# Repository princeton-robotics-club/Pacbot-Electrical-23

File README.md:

View this project on [CADLAB.io](https://cadlab.io/project/26145). 

# Pacbot-Electrical-22-23

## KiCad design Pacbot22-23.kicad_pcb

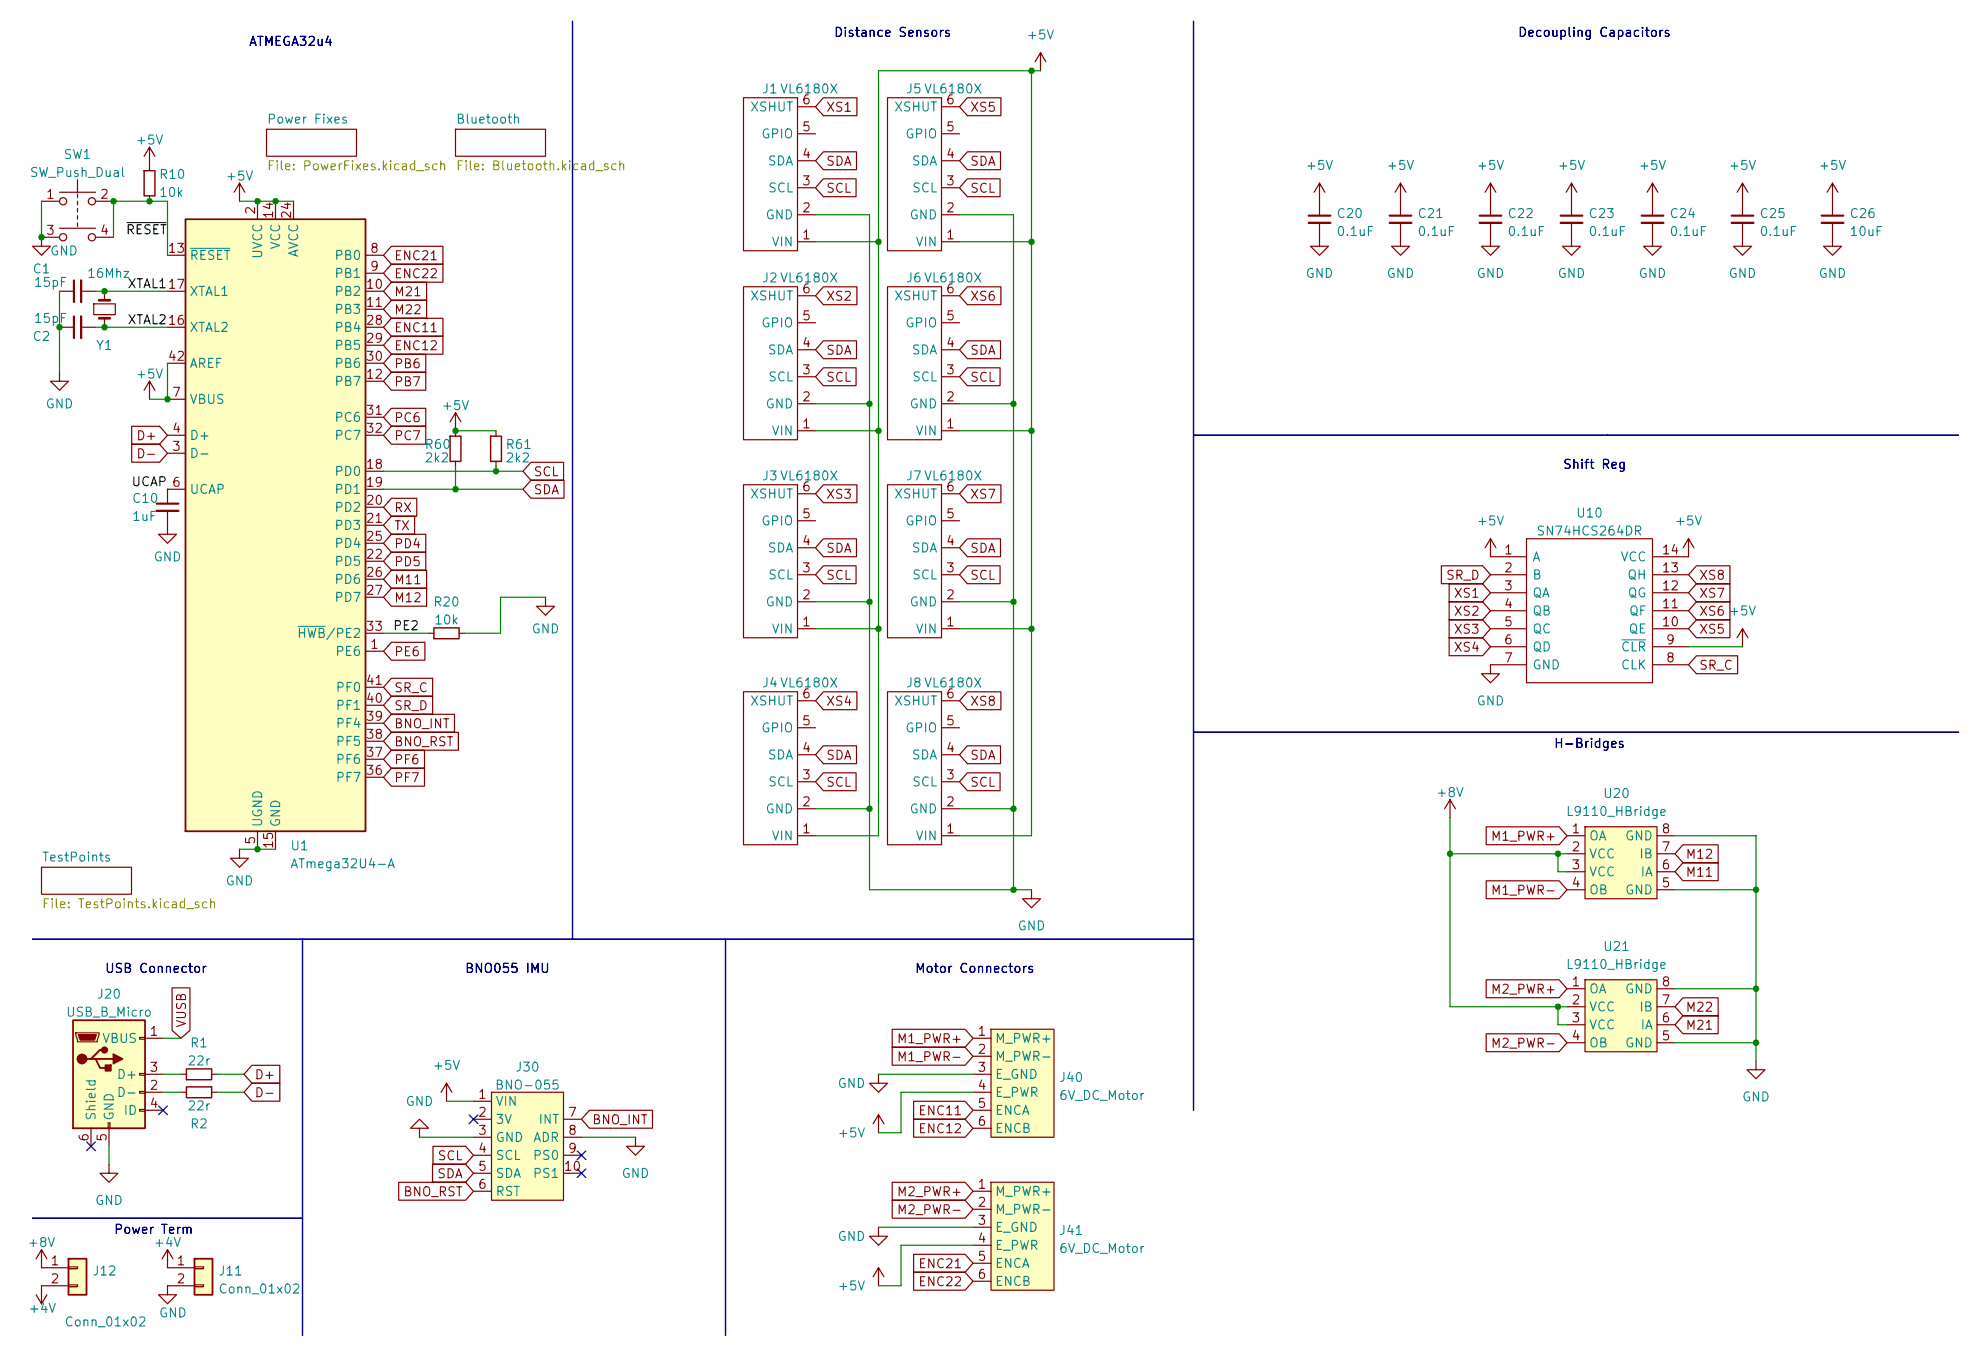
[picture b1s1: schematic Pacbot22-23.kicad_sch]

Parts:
C1, C2: 15pF; C_0805_2012Metric
C10: 1uF; C_0805_2012Metric
C20, C21, C22, C23, C24, C25: 0.1uF; C_0805_2012Metric
C26: 10uF; C_0805_2012Metric
J1, J2, J3, J4, J5, J6, J7, J8: VL6180X
J11, J12: Conn_01x02; POWER_TERM
J20: USB_B_Micro; USB_Micro-B_GCT_USB3076-30-A
J30: BNO-055; BNO055
J40, J41: 6V_DC_Motor
R1, R2: 22r; R_0805_2012Metric
R10, R20: 10k; R_0805_2012Metric
R60, R61: 2k2; R_0805_2012Metric
SW1: SW_Push_Dual; TL3305AF260QG
U1: ATmega32U4-A; TQFP-44_10x10mm_P0.8mm
U10: SN74HCS264DR; SOIC127P600X175-14N; Mouser Part Number 595-SN74HCS264DR
U20, U21: L9110_HBridge; Adafruit_L9110_HBridge
Y1: 16Mhz; Crystal_SMD_5032-2Pin_5.0x3.2mm_HandSoldering

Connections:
+4V: J11.1, J12.2
+5V: C20.1, C21.1, C22.1, C23.1, C24.1, C25.1, C26.1, J1.1 (VIN), J2.1 (VIN), J3.1 (VIN), J4.1 (VIN), J5.1 (VIN), J6.1 (VIN), J7.1 (VIN), J8.1 (VIN), J30.1 (VIN), J40.4 (E_PWR), J41.4 (E_PWR), R10.1, R60.1, R61.1, U1.2 (UVCC), U1.7 (VBUS), U1.14 (VCC), U1.24 (AVCC), U1.34 (VCC), U1.42 (AREF), U1.44 (AVCC), U10.1 (A), U10.9 (~CLR), U10.14 (VCC); also elsewhere on the board
+8V: J12.1, U20.2 (VCC), U20.3 (VCC), U21.2 (VCC), U21.3 (VCC); also elsewhere on the board
/PE2: R20.1, U1.33 (~HWB/PE2)
/UCAP: C10.1, U1.6 (UCAP)
/XTAL1: C1.2, U1.17 (XTAL1), Y1.1
/XTAL2: C2.2, U1.16 (XTAL2), Y1.2
/~RESET: R10.2, SW1.2, SW1.4, U1.13 (~RESET)
BNO_INT: J30.7 (INT), U1.39 (PF4); also elsewhere on the board
BNO_RST: J30.6 (RST), U1.38 (PF5); also elsewhere on the board
D+: R1.2, U1.4 (D+); also elsewhere on the board
D-: R2.1, U1.3 (D-); also elsewhere on the board
ENC11: J40.5 (ENCA), U1.28 (PB4); also elsewhere on the board
ENC12: J40.6 (ENCB), U1.29 (PB5); also elsewhere on the board
ENC21: J41.5 (ENCA), U1.8 (PB0); also elsewhere on the board
ENC22: J41.6 (ENCB), U1.9 (PB1); also elsewhere on the board
GND: C1.1, C2.1, C10.2, C20.2, C21.2, C22.2, C23.2, C24.2, C25.2, C26.2, J1.2 (GND), J2.2 (GND), J3.2 (GND), J4.2 (GND), J5.2 (GND), J6.2 (GND), J7.2 (GND), J8.2 (GND), J11.2, J20.5 (GND), J30.3 (GND), J30.8 (ADR), J40.3 (E_GND), J41.3 (E_GND), R20.2, SW1.1, SW1.3, U1.5 (UGND), U1.15 (GND), U1.23 (GND), U1.35 (GND), U1.43 (GND), U10.7 (GND), U20.5 (GND), U20.8 (GND), U21.5 (GND), U21.8 (GND); also elsewhere on the board
M1_PWR+: J40.1 (M_PWR+), U20.1 (OA)
M1_PWR-: J40.2 (M_PWR-), U20.4 (OB)
M2_PWR+: J41.1 (M_PWR+), U21.1 (OA)
M2_PWR-: J41.2 (M_PWR-), U21.4 (OB)
M11: U1.26 (PD6), U20.6 (IA); also elsewhere on the board
M12: U1.27 (PD7), U20.7 (IB); also elsewhere on the board
M21: U1.10 (PB2), U21.6 (IA); also elsewhere on the board
M22: U1.11 (PB3), U21.7 (IB); also elsewhere on the board
unnamed: J20.2 (D-), R2.2
unnamed: J20.3 (D+), R1.1
PB6: U1.30 (PB6); also elsewhere on the board
PB7: U1.12 (PB7); also elsewhere on the board
PC6: U1.31 (PC6); also elsewhere on the board
PC7: U1.32 (PC7); also elsewhere on the board
PD4: U1.25 (PD4); also elsewhere on the board
PD5: U1.22 (PD5); also elsewhere on the board
PE6: U1.1 (PE6); also elsewhere on the board
PF6: U1.37 (PF6); also elsewhere on the board
PF7: U1.36 (PF7); also elsewhere on the board
RX: U1.20 (PD2); also elsewhere on the board
SCL: J1.3 (SCL), J2.3 (SCL), J3.3 (SCL), J4.3 (SCL), J5.3 (SCL), J6.3 (SCL), J7.3 (SCL), J8.3 (SCL), J30.4 (SCL), R61.2, U1.18 (PD0); also elsewhere on the board
SDA: J1.4 (SDA), J2.4 (SDA), J3.4 (SDA), J4.4 (SDA), J5.4 (SDA), J6.4 (SDA), J7.4 (SDA), J8.4 (SDA), J30.5 (SDA), R60.2, U1.19 (PD1); also elsewhere on the board
SR_C: U1.41 (PF0), U10.8 (CLK); also elsewhere on the board
SR_D: U1.40 (PF1), U10.2 (B); also elsewhere on the board
TX: U1.21 (PD3); also elsewhere on the board
VUSB: J20.1 (VBUS); also elsewhere on the board
XS1: J1.6 (XSHUT), U10.3 (QA)
XS2: J2.6 (XSHUT), U10.4 (QB)
XS3: J3.6 (XSHUT), U10.5 (QC)
XS4: J4.6 (XSHUT), U10.6 (QD)
XS5: J5.6 (XSHUT), U10.10 (QE)
XS6: J6.6 (XSHUT), U10.11 (QF)
XS7: J7.6 (XSHUT), U10.12 (QG)
XS8: J8.6 (XSHUT), U10.13 (QH)

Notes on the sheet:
ATMEGA32u4
Shift Reg
USB Connector
Power Term
H-Bridges
BNO055 IMU
Distance Sensors
Decoupling Capacitors
Motor Connectors

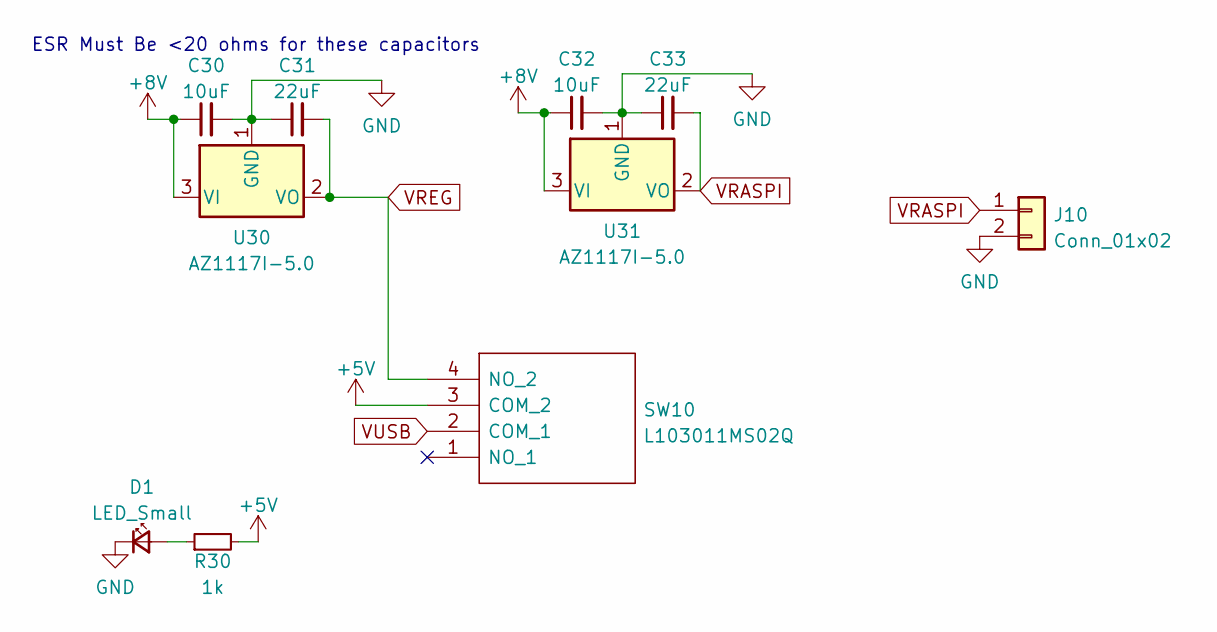
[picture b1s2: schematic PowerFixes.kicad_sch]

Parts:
C30, C32: 10uF; C_0805_2012Metric
C31, C33: 22uF; C_0805_2012Metric
D1: LED_Small; D_0805_2012Metric
J10: Conn_01x02; POWER_TERM
R30: 1k; R_0805_2012Metric
SW10: L103011MS02Q; Mouser Part Number 611-L103011MS02Q
U30, U31: AZ1117I-5.0; SOT-223-3_TabPin2

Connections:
+5V: R30.2, SW10.3 (COM_2); also elsewhere on the board
+8V: C30.1, C32.1, U30.3 (VI), U31.3 (VI); also elsewhere on the board
GND: C30.2, C31.1, C32.2, C33.1, D1.1 (K), J10.2, U30.1 (GND), U31.1 (GND); also elsewhere on the board
unnamed: D1.2 (A), R30.1
VRASPI: C33.2, J10.1, U31.2 (VO)
VREG: C31.2, SW10.4 (NO_2), U30.2 (VO); also elsewhere on the board
VUSB: SW10.2 (COM_1); also elsewhere on the board

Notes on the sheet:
ESR Must Be <20 ohms for these capacitors

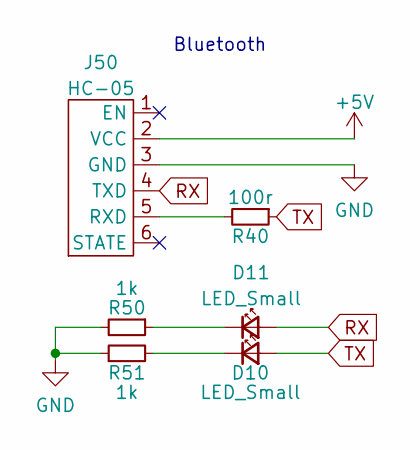
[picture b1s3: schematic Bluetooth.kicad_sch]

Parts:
D10, D11: LED_Small; D_0805_2012Metric
J50: HC-05
R40: 100r; R_0805_2012Metric
R50, R51: 1k; R_0805_2012Metric

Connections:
+5V: J50.2 (VCC); also elsewhere on the board
GND: J50.3 (GND), R50.2, R51.1; also elsewhere on the board
unnamed: D10.1 (K), R51.2
unnamed: D11.1 (K), R50.1
unnamed: J50.5 (RXD), R40.2
RX: D11.2 (A), J50.4 (TXD); also elsewhere on the board
TX: D10.2 (A), R40.1; also elsewhere on the board

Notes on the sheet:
Bluetooth

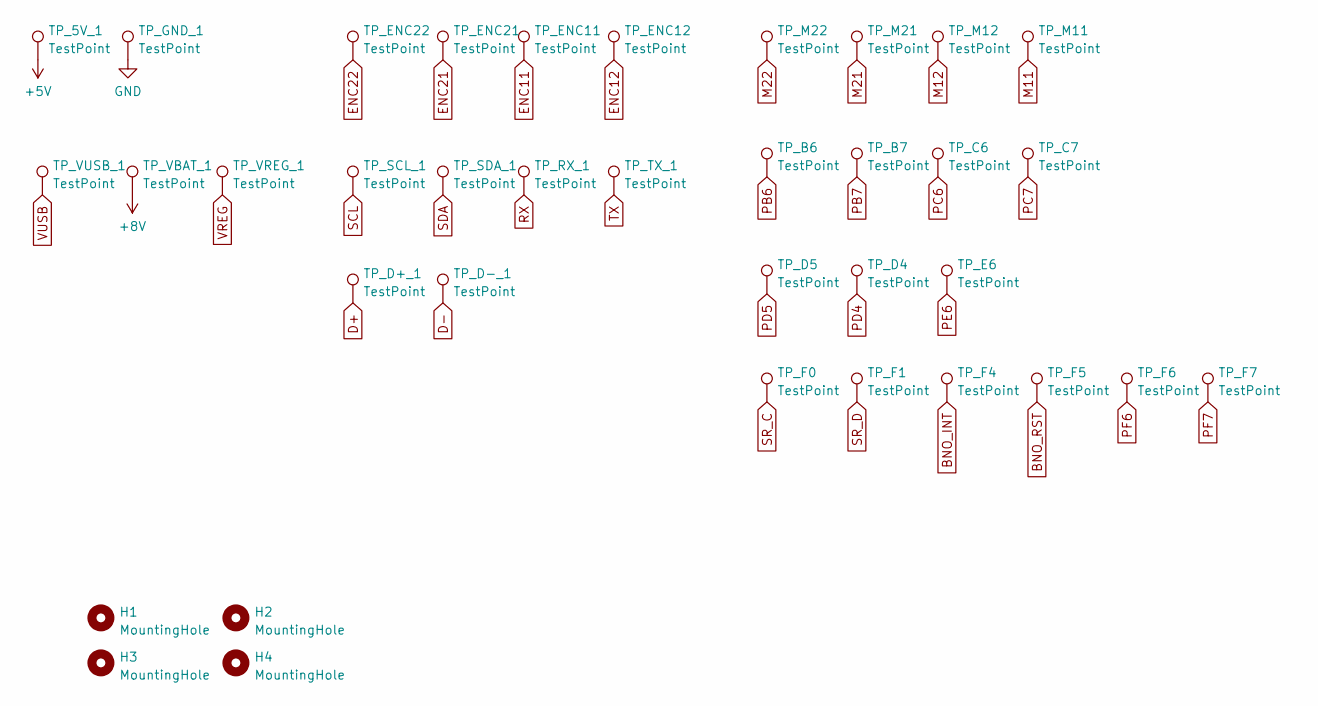
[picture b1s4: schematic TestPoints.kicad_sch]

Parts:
H1, H2, H3, H4: MountingHole; MountingHole_2.5mm_Pad
TP_5V_1: TestPoint; TestPoint_Pad_D1.5mm
TP_B6, TP_B7: TestPoint; TestPoint_Pad_D1.5mm
TP_C6, TP_C7: TestPoint; TestPoint_Pad_D1.5mm
TP_D4, TP_D5: TestPoint; TestPoint_Pad_D1.5mm
TP_D+_1: TestPoint; TestPoint_Pad_D1.5mm
TP_D-_1: TestPoint; TestPoint_Pad_D1.5mm
TP_E6: TestPoint; TestPoint_Pad_D1.5mm
TP_ENC11, TP_ENC12, TP_ENC21, TP_ENC22: TestPoint; TestPoint_Pad_D1.5mm
TP_F0, TP_F1, TP_F4, TP_F5, TP_F6, TP_F7: TestPoint; TestPoint_Pad_D1.5mm
TP_GND_1: TestPoint; TestPoint_Pad_D1.5mm
TP_M11, TP_M12, TP_M21, TP_M22: TestPoint; TestPoint_Pad_D1.5mm
TP_RX_1: TestPoint; TestPoint_Pad_D1.5mm
TP_SCL_1: TestPoint; TestPoint_Pad_D1.5mm
TP_SDA_1: TestPoint; TestPoint_Pad_D1.5mm
TP_TX_1: TestPoint; TestPoint_Pad_D1.5mm
TP_VBAT_1: TestPoint; TestPoint_Pad_D1.5mm
TP_VREG_1: TestPoint; TestPoint_Pad_D1.5mm
TP_VUSB_1: TestPoint; TestPoint_Pad_D1.5mm

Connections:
+5V: TP_5V_1.1; also elsewhere on the board
+8V: TP_VBAT_1.1; also elsewhere on the board
BNO_INT: TP_F4.1; also elsewhere on the board
BNO_RST: TP_F5.1; also elsewhere on the board
D+: TP_D+_1.1; also elsewhere on the board
D-: TP_D-_1.1; also elsewhere on the board
ENC11: TP_ENC11.1; also elsewhere on the board
ENC12: TP_ENC12.1; also elsewhere on the board
ENC21: TP_ENC21.1; also elsewhere on the board
ENC22: TP_ENC22.1; also elsewhere on the board
GND: TP_GND_1.1; also elsewhere on the board
M11: TP_M11.1; also elsewhere on the board
M12: TP_M12.1; also elsewhere on the board
M21: TP_M21.1; also elsewhere on the board
M22: TP_M22.1; also elsewhere on the board
PB6: TP_B6.1; also elsewhere on the board
PB7: TP_B7.1; also elsewhere on the board
PC6: TP_C6.1; also elsewhere on the board
PC7: TP_C7.1; also elsewhere on the board
PD4: TP_D4.1; also elsewhere on the board
PD5: TP_D5.1; also elsewhere on the board
PE6: TP_E6.1; also elsewhere on the board
PF6: TP_F6.1; also elsewhere on the board
PF7: TP_F7.1; also elsewhere on the board
RX: TP_RX_1.1; also elsewhere on the board
SCL: TP_SCL_1.1; also elsewhere on the board
SDA: TP_SDA_1.1; also elsewhere on the board
SR_C: TP_F0.1; also elsewhere on the board
SR_D: TP_F1.1; also elsewhere on the board
TX: TP_TX_1.1; also elsewhere on the board
VREG: TP_VREG_1.1; also elsewhere on the board
VUSB: TP_VUSB_1.1; also elsewhere on the board

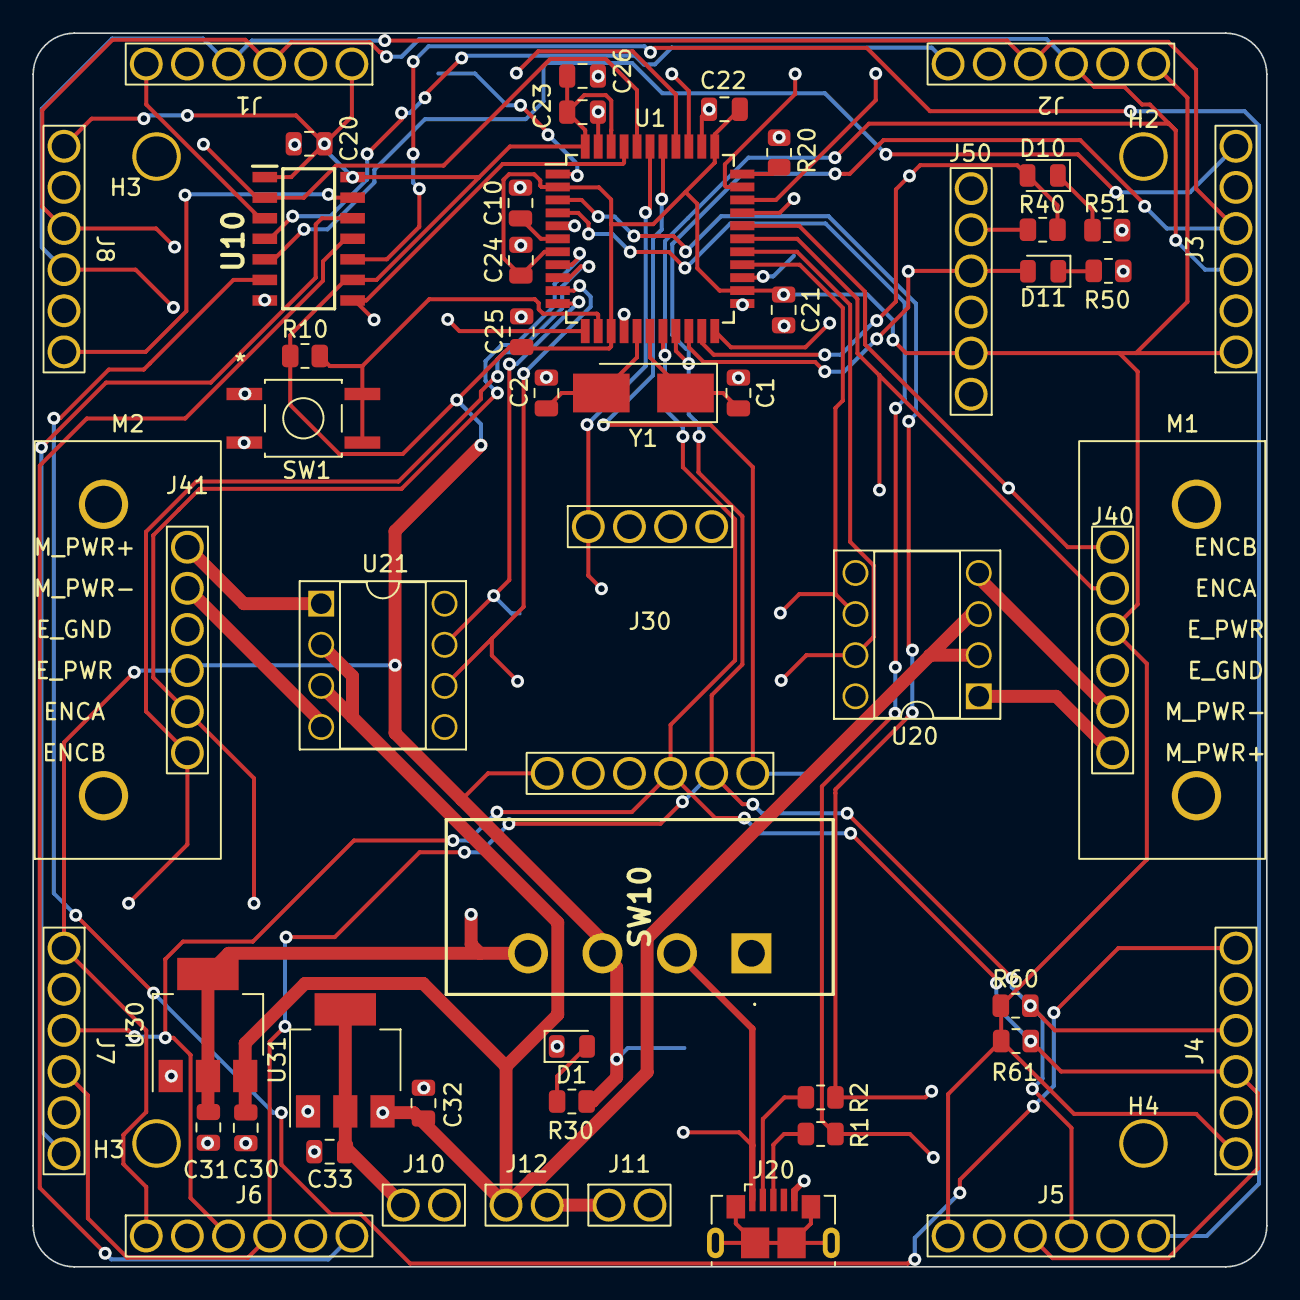
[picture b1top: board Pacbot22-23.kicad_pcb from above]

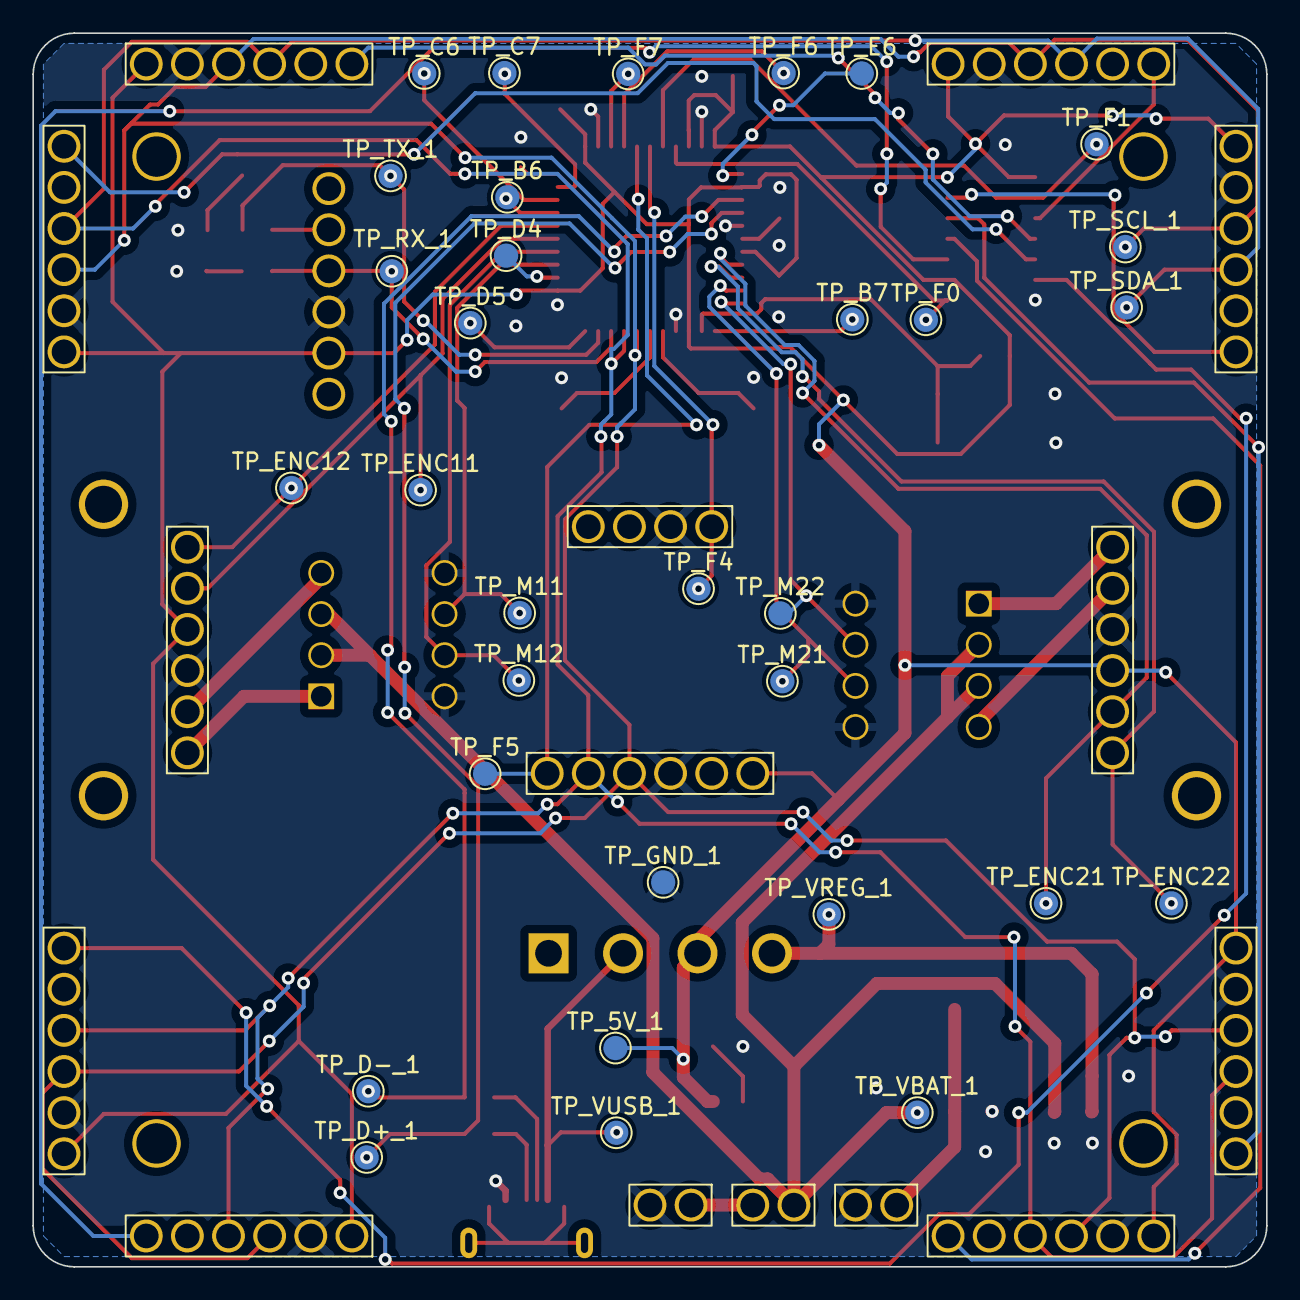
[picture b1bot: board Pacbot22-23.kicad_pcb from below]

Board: 2 copper layers, 76.2 x 76.2 mm, 90 parts (32 on the bottom side), 57 nets.

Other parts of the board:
H3#2: MountingHole; MountingHole_2.5mm_Pad
M1: M1_Mount; Motor_Mount
M2: M2_Mount; Motor_Mount

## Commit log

2022-09-22 Updated the .gitignore
2022-09-22 Removed files that were in gitignore
2022-10-31 Created a custom symbol library
2022-10-31 Moved symbols
2022-10-31 Backlink to CADLAB.io has been added.
2022-10-31 added second test symbol
2022-10-31 Added third symbol
2022-10-31 Removed a sym
2022-10-31 Forth Simble
2022-10-31 Added PCB edges
2022-11-01 Removed fake test symbols
2022-11-02 Setup for symbol and footprint training
2022-11-02 Custom footprints pretty folder question mark?
2022-11-02 adding the footprint library
2022-11-05 added sample symbol and footprint
2022-11-10 My schtuff
2022-11-10 Updated libs
2022-11-10 Updated Libs 2
2022-11-12 VL6180X symbol & footprint
2022-11-12 add HC-05
2022-11-12 Added VL6180x symbol and footprint
2022-11-12 Added Symbols and Footprints
2022-11-12 HC-05 Symbol and Footprint
2022-11-12 added symbol and footprint for 6V DC motors
2022-11-12 Symbol and Footprint for 6V DC Motor
2022-11-12 Hello
2022-11-13 backup
2022-11-13 Tiny changes associated with proper merging
2022-11-14 Finished backup of schematic
2022-11-14 Fixed question mark issue
2022-11-14 Added bluetooth schematic lmao my b for not putting this on the original
2022-11-16 Added LVR
2022-11-18 added H-bridges schematic
2022-11-19 Shift Register Schematic
2022-11-19 Distance Sensors [FH]
2022-11-19 Added power term to schematic
2022-11-19 Pushing test
2022-11-19 schematic design
2022-11-19 hello 2
2022-11-19 BNO055 schematic
2022-11-20 Push bluetooth
2022-11-20 Merged in everyone's schematic changes
2022-11-20 Finishing touches (associating footprints) to schematic
2022-11-20 Finishing touches 2 (extra test points)
2022-11-28 Pushing PCB
2022-12-04 Changes... James Changes
2022-12-05 Final PCB

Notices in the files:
parts and their libraries:
Copyright 2021 Accelerated Designs. All rights reserved.
